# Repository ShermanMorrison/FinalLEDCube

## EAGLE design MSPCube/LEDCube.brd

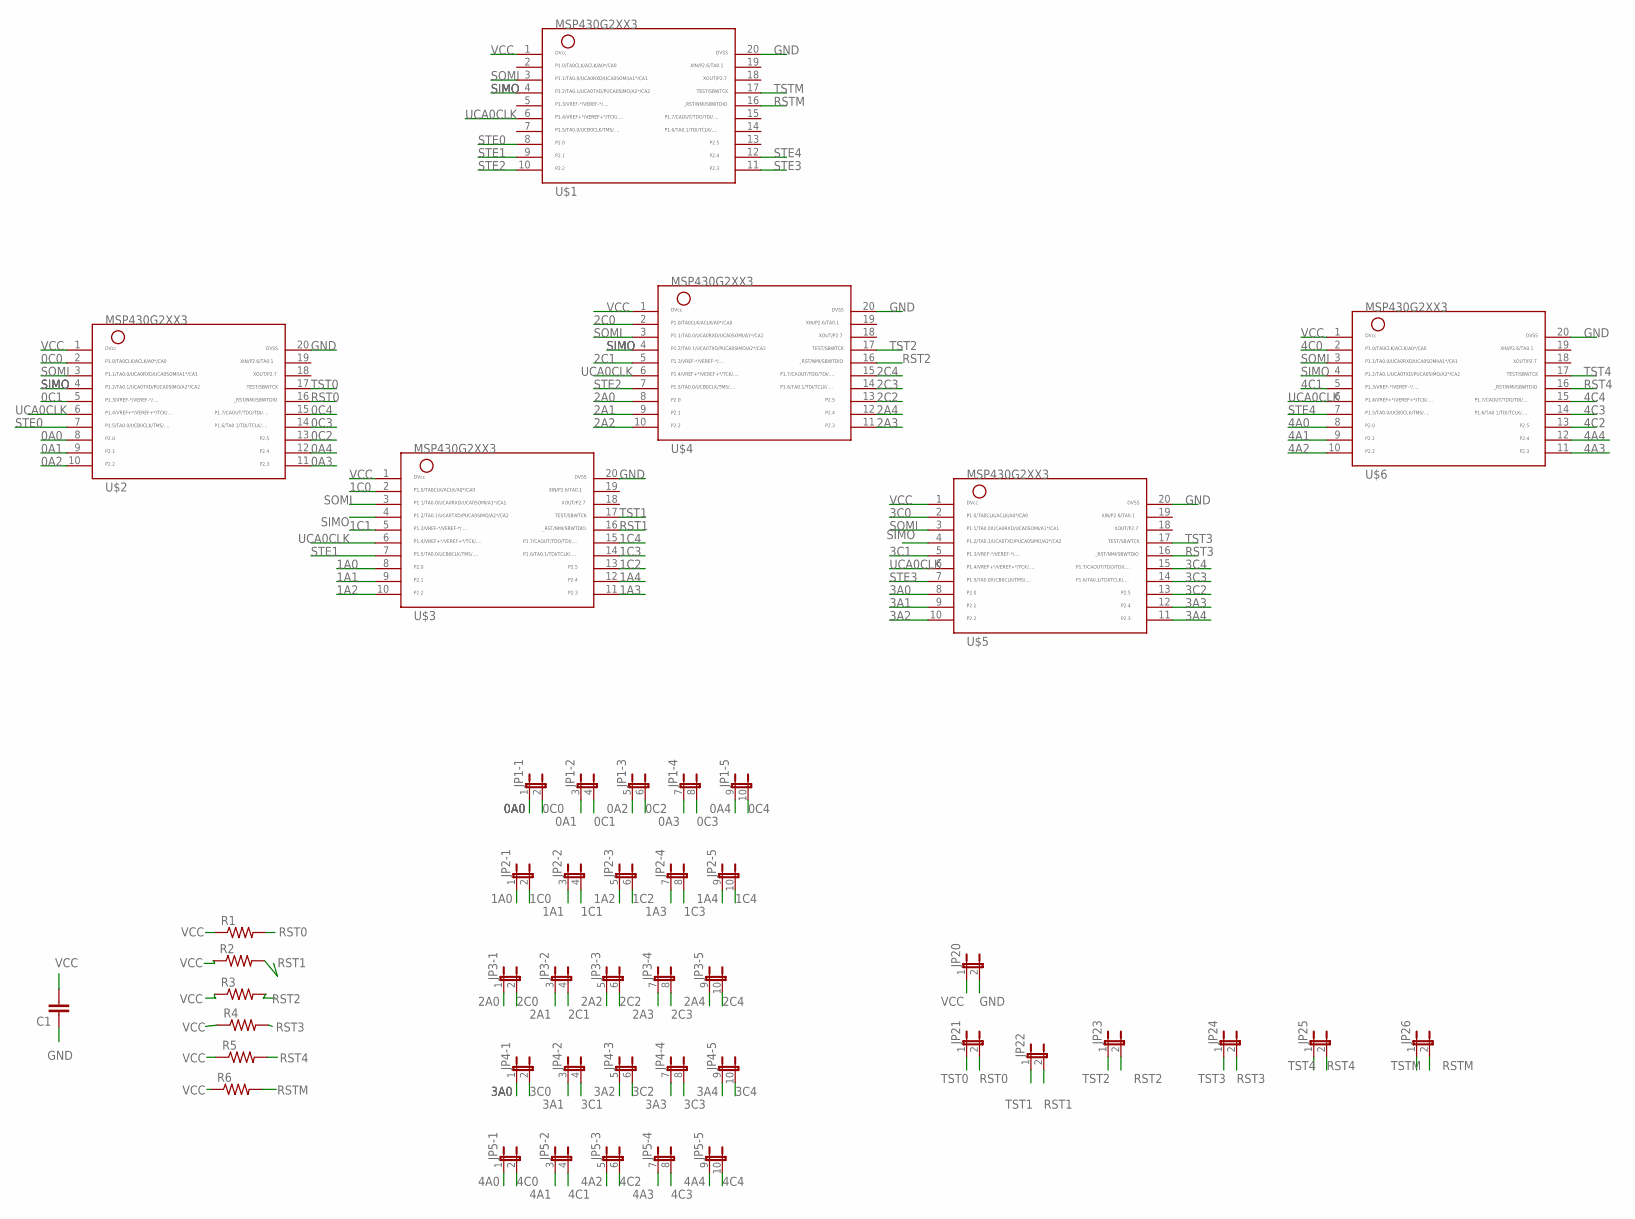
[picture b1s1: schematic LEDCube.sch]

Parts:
C1: CC1206; C1206
JP1, JP2, JP3, JP4, JP5: JP5QE; JP5Q
JP20, JP21, JP22, JP23, JP24, JP25, JP26: JP1E; JP1
R1, R2, R3, R4, R5, R6: R-US_R1206; R1206
U$1, U$2, U$3, U$4, U$5, U$6: MSP430G2XX3TSSOP; PW20

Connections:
0A0: JP1.1, U$2.8
0A1: JP1.3 (1), U$2.9
0A2: JP1.5 (1), U$2.10
0A3: JP1.7 (1), U$2.11
0A4: JP1.9 (1), U$2.12
0C0: JP1.2, U$2.2
0C1: JP1.4 (2), U$2.5
0C2: JP1.6 (2), U$2.13
0C3: JP1.8 (2), U$2.14
0C4: JP1.10 (2), U$2.15
1A0: JP2.1, U$3.8
1A1: JP2.3 (1), U$3.9
1A2: JP2.5 (1), U$3.10
1A3: JP2.7 (1), U$3.11
1A4: JP2.9 (1), U$3.12
1C0: JP2.2, U$3.2
1C1: JP2.4 (2), U$3.5
1C2: JP2.6 (2), U$3.13
1C3: JP2.8 (2), U$3.14
1C4: JP2.10 (2), U$3.15
2A0: JP3.1, U$4.8
2A1: JP3.3 (1), U$4.9
2A2: JP3.5 (1), U$4.10
2A3: JP3.7 (1), U$4.11
2A4: JP3.9 (1), U$4.12
2C0: JP3.2, U$4.2
2C1: JP3.4 (2), U$4.5
2C2: JP3.6 (2), U$4.13
2C3: JP3.8 (2), U$4.14
2C4: JP3.10 (2), U$4.15
3A0: JP4.1, U$5.8
3A1: JP4.3 (1), U$5.9
3A2: JP4.5 (1), U$5.10
3A3: JP4.7 (1), U$5.12
3A4: JP4.9 (1), U$5.11
3C0: JP4.2, U$5.2
3C1: JP4.4 (2), U$5.5
3C2: JP4.6 (2), U$5.13
3C3: JP4.8 (2), U$5.14
3C4: JP4.10 (2), U$5.15
4A0: JP5.1, U$6.8
4A1: JP5.3 (1), U$6.9
4A2: JP5.5 (1), U$6.10
4A3: JP5.7 (1), U$6.11
4A4: JP5.9 (1), U$6.12
4C0: JP5.2, U$6.2
4C1: JP5.4 (2), U$6.5
4C2: JP5.6 (2), U$6.13
4C3: JP5.8 (2), U$6.14
4C4: JP5.10 (2), U$6.15
GND: C1.1, JP20.2, U$1.20, U$2.20, U$3.20, U$4.20, U$5.20, U$6.20
RST0: JP21.2, R1.2, U$2.16
RST1: JP22.2, R2.2, U$3.16
RST2: JP23.2, R3.2, U$4.16
RST3: JP24.2, R4.2, U$5.16
RST4: JP25.2, R5.2, U$6.16
RSTM: JP26.2, R6.2, U$1.16
SIMO: U$1.4, U$2.4, U$3.4, U$4.4, U$5.4, U$6.4
SOMI: U$1.3, U$2.3, U$3.3, U$4.3, U$5.3, U$6.3
STE0: U$1.8, U$2.7
STE1: U$1.9, U$3.7
STE2: U$1.10, U$4.7
STE3: U$1.11, U$5.7
STE4: U$1.12, U$6.7
TST0: JP21.1, U$2.17
TST1: JP22.1, U$3.17
TST2: JP23.1, U$4.17
TST3: JP24.1, U$5.17
TST4: JP25.1, U$6.17
TSTM: JP26.1, U$1.17
UCA0CLK: U$1.6, U$2.6, U$3.6, U$4.6, U$5.6, U$6.6
VCC: C1.2, JP20.1, R1.1, R2.1, R3.1, R4.1, R5.1, R6.1, U$1.1, U$2.1, U$3.1, U$4.1, U$5.1, U$6.1

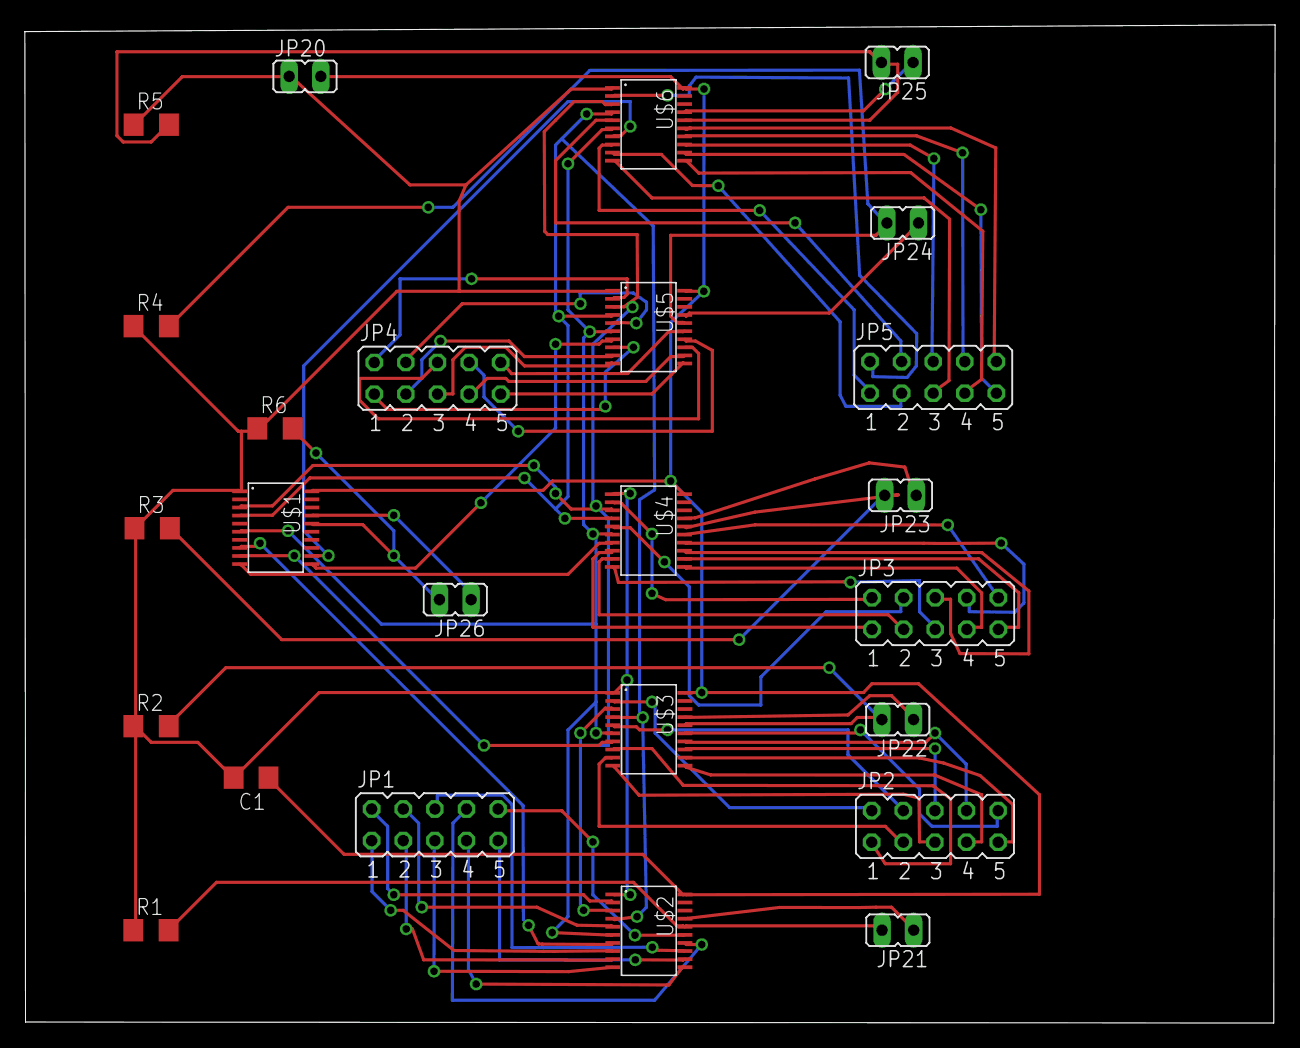
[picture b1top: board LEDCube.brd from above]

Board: 2 copper layers, 100.5 x 80.2 mm, 25 parts (0 on the bottom side), 72 nets.

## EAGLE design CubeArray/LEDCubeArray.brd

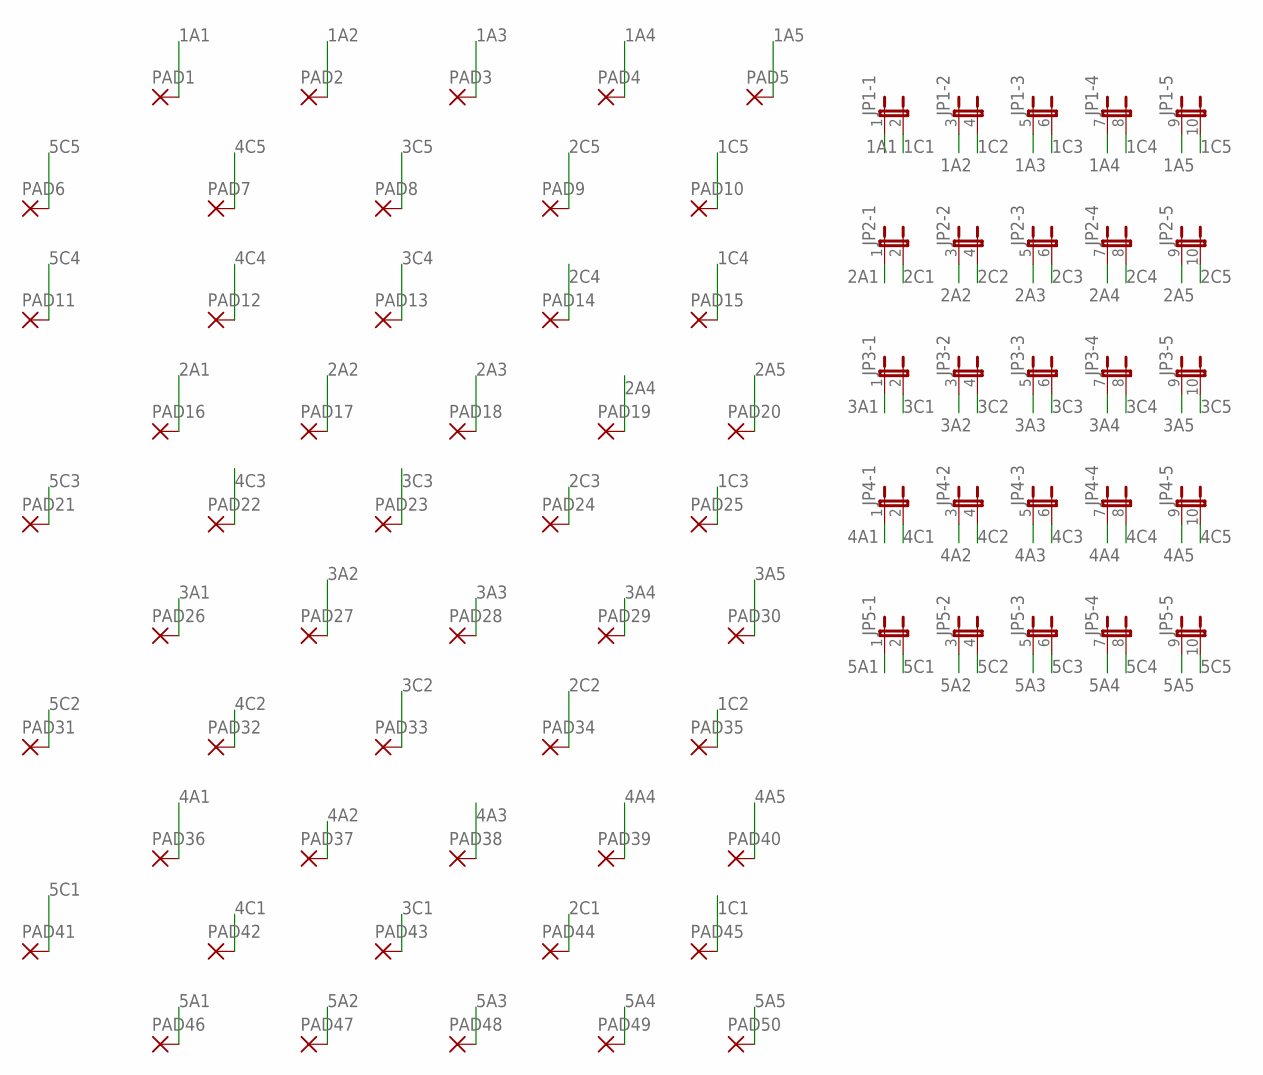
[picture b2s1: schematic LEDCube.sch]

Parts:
JP1, JP2, JP3, JP4, JP5: JP5QE; JP5Q
PAD1, PAD2, PAD3, PAD4, PAD5, PAD6, PAD7, PAD8, PAD9, PAD10, PAD11, PAD12, PAD13, PAD14, PAD15, PAD16, PAD17, PAD18, PAD19, PAD20, PAD21, PAD22, PAD23, PAD24, PAD25, PAD26, PAD27, PAD28, PAD29, PAD30, PAD31, PAD32, PAD33, PAD34, PAD35, PAD36, PAD37, PAD38, PAD39, PAD40, PAD41, PAD42, PAD43, PAD44, PAD45, PAD46, PAD47, PAD48, PAD49, PAD50: 2,54/1,1

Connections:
1A1: JP1.1, PAD1.1
1A2: JP1.3 (1), PAD2.1
1A3: JP1.5 (1), PAD3.1
1A4: JP1.7 (1), PAD4.1
1A5: JP1.9 (1), PAD5.1
1C1: JP1.2, PAD45.1
1C2: JP1.4 (2), PAD35.1
1C3: JP1.6 (2), PAD25.1
1C4: JP1.8 (2), PAD15.1
1C5: JP1.10 (2), PAD10.1
2A1: JP2.1, PAD16.1
2A2: JP2.3 (1), PAD17.1
2A3: JP2.5 (1), PAD18.1
2A4: JP2.7 (1), PAD19.1
2A5: JP2.9 (1), PAD20.1
2C1: JP2.2, PAD44.1
2C2: JP2.4 (2), PAD34.1
2C3: JP2.6 (2), PAD24.1
2C4: JP2.8 (2), PAD14.1
2C5: JP2.10 (2), PAD9.1
3A1: JP3.1, PAD26.1
3A2: JP3.3 (1), PAD27.1
3A3: JP3.5 (1), PAD28.1
3A4: JP3.7 (1), PAD29.1
3A5: JP3.9 (1), PAD30.1
3C1: JP3.2, PAD43.1
3C2: JP3.4 (2), PAD33.1
3C3: JP3.6 (2), PAD23.1
3C4: JP3.8 (2), PAD13.1
3C5: JP3.10 (2), PAD8.1
4A1: JP4.1, PAD36.1
4A2: JP4.3 (1), PAD37.1
4A3: JP4.5 (1), PAD38.1
4A4: JP4.7 (1), PAD39.1
4A5: JP4.9 (1), PAD40.1
4C1: JP4.2, PAD42.1
4C2: JP4.4 (2), PAD32.1
4C3: JP4.6 (2), PAD22.1
4C4: JP4.8 (2), PAD12.1
4C5: JP4.10 (2), PAD7.1
5A1: JP5.1, PAD46.1
5A2: JP5.3 (1), PAD47.1
5A3: JP5.5 (1), PAD48.1
5A4: JP5.7 (1), PAD49.1
5A5: JP5.9 (1), PAD50.1
5C1: JP5.2, PAD41.1
5C2: JP5.4 (2), PAD31.1
5C3: JP5.6 (2), PAD21.1
5C4: JP5.8 (2), PAD11.1
5C5: JP5.10 (2), PAD6.1

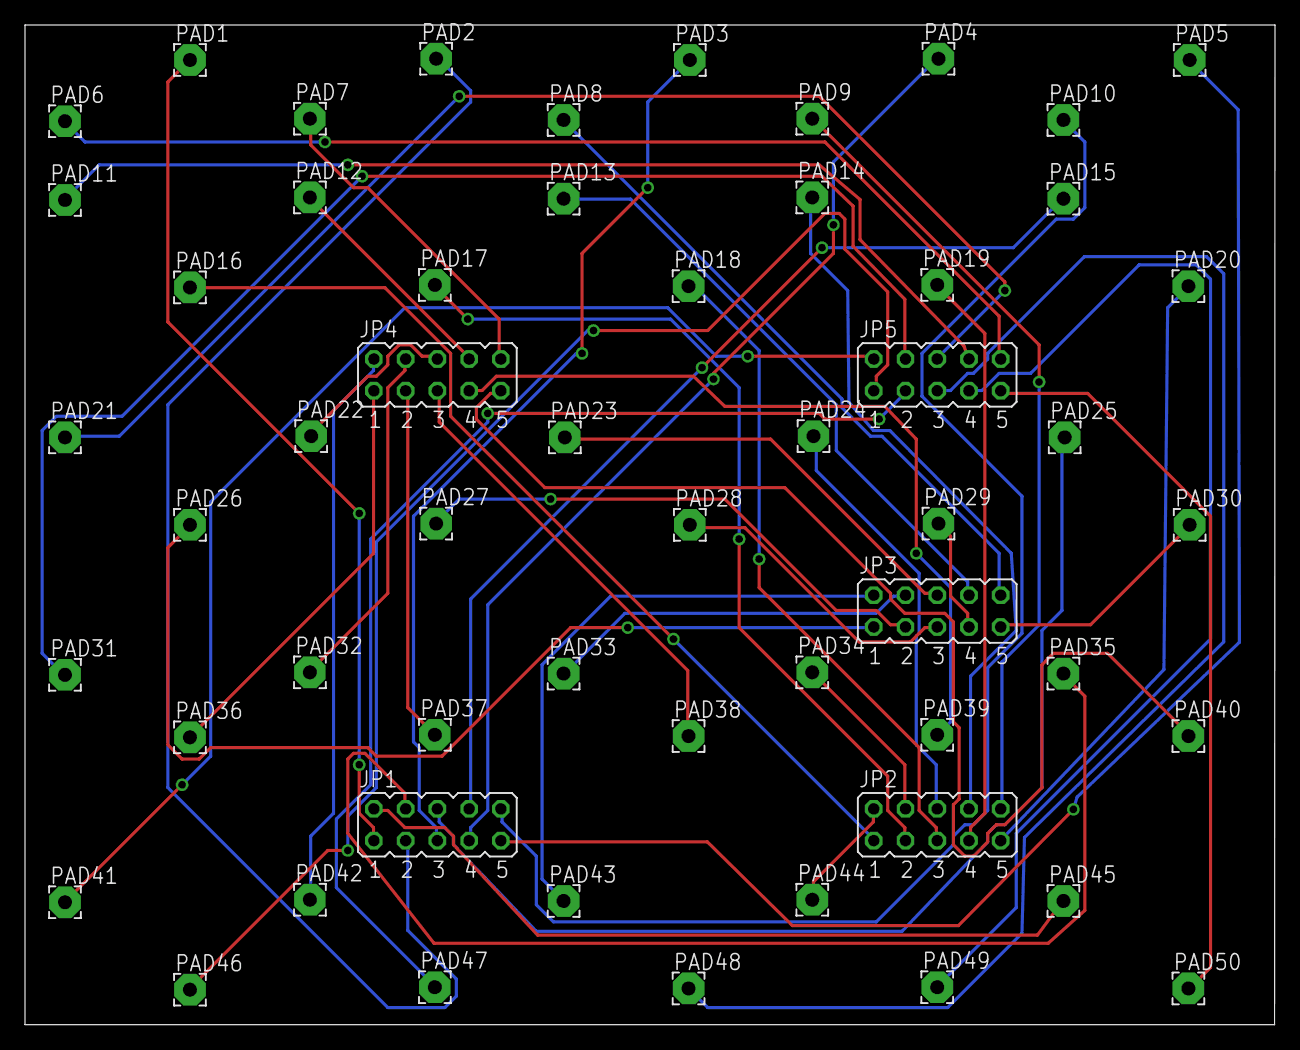
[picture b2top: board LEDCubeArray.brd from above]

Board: 2 copper layers, 100.0 x 80.0 mm, 55 parts (0 on the bottom side), 50 nets.

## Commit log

2015-04-27 init
2015-04-27 Laid out MSP430 board. Not routed yet.
2015-04-27 LED array PCB
2015-04-28 Routed PCB Array Board
2015-04-28 "LED cube MSP430 PCB that passes DRC and ERC"
2015-05-04 printed version
